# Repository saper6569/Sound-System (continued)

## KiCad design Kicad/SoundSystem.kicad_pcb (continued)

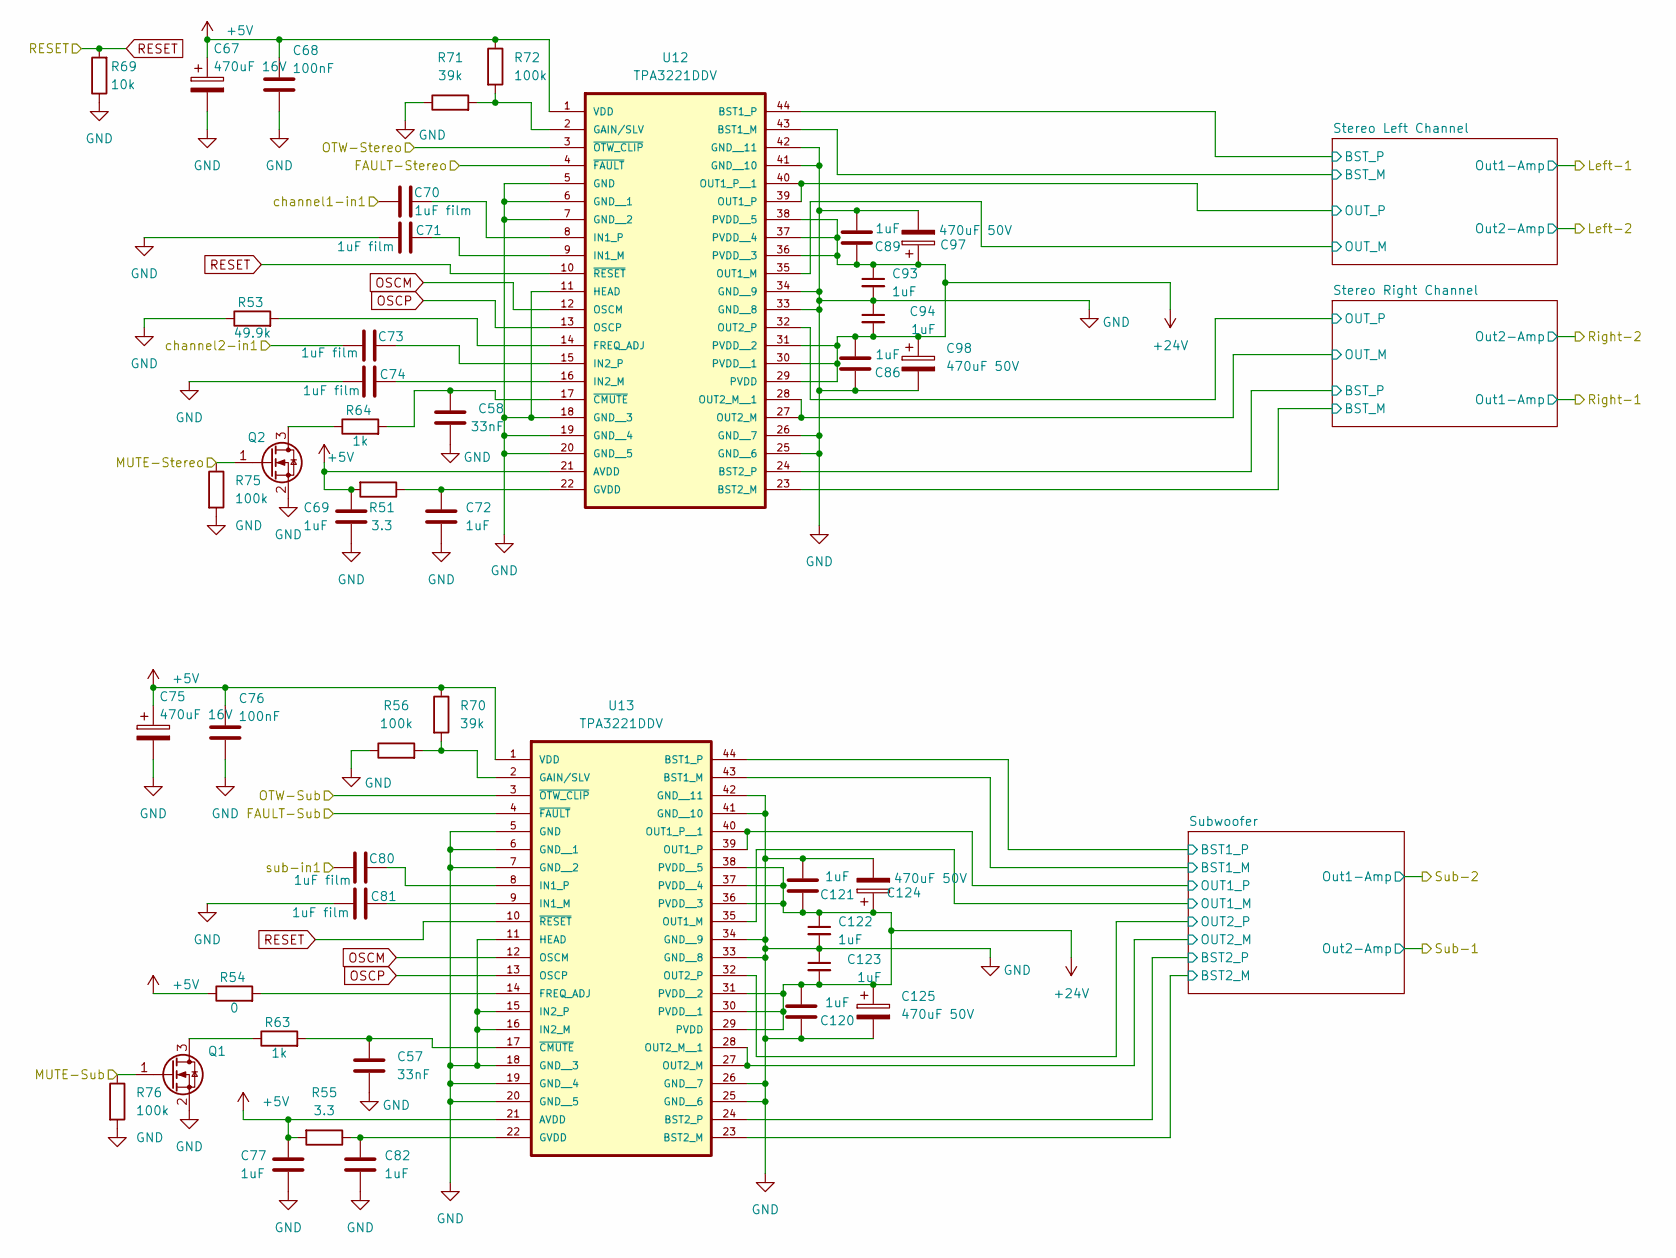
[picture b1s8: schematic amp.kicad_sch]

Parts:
C57, C58: 33nF; C_0805_2012Metric_Pad1.18x1.45mm_HandSolder; MPN CC0805KRX7R9BB333; LCSC C107150
C67, C75: 470uF 16V; CP_Elec_10x10; MPN RYRVT16V470UF10*10; LCSC C48970774
C68, C76: 100nF; C_0805_2012Metric_Pad1.18x1.45mm_HandSolder; MPN CC0805KRX7R9BB104; LCSC C49678
C69, C72, C77, C82: 1uF; C_0805_2012Metric_Pad1.18x1.45mm_HandSolder; MPN CC0805KKX7R9BB105; LCSC C91185
C70, C71, C73, C74, C80, C81: 1uF film; C_Rect_L7.2mm_W5.5mm_P5.00mm_FKS2_FKP2_MKS2_MKP2; MPN B32529C0105J289; LCSC C125386
C86, C89, C93, C94, C120, C121, C122, C123: 1uF; C_1206_3216Metric_Pad1.33x1.80mm_HandSolder; MPN CC1206KKX7R9BB105; LCSC C107185
C97, C98, C124, C125: 470uF 50V; CP_Radial_D12.5mm_P5.00mm; MPN NXH 50V470 12.5*20; LCSC C165672
Q1, Q2: 2N7002; TO-236AB_SOT23_NEX; MPN 2N7002; LCSC C8545
R51, R55: 3.3; R_0603_1608Metric_Pad0.98x0.95mm_HandSolder; MPN 0603WAF330KT5E; LCSC C22979
R53: 49.9k; R_0805_2012Metric_Pad1.20x1.40mm_HandSolder; MPN 0805W8F4992T5E; LCSC C17719
R54: 0; R_0805_2012Metric_Pad1.20x1.40mm_HandSolder; MPN 0805W8F0000T5E; LCSC C17477
R56, R72: 100k; R_0603_1608Metric_Pad0.98x0.95mm_HandSolder; MPN 0603WAF1003T5E; LCSC C25803
R63, R64: 1k; R_0805_2012Metric_Pad1.20x1.40mm_HandSolder; MPN 0805W8F1001T5E; LCSC C17513
R69: 10k; R_0805_2012Metric_Pad1.20x1.40mm_HandSolder; MPN 0805W8F1002T5E; LCSC C17414
R70, R71: 39k; R_0805_2012Metric_Pad1.20x1.40mm_HandSolder; MPN 0805W8F3902T5E; LCSC C25826
R75, R76: 100k; R_0805_2012Metric_Pad1.20x1.40mm_HandSolder; MPN 0805W8F1003T5E; LCSC C17407
U12, U13: TPA3221DDV; MPN TPA3221DDVR; LCSC C475500

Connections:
/Amplifier/FAULT-Stereo: U12.4 (~FAULT); also elsewhere on the board
/Amplifier/FAULT-Sub: U13.4 (~FAULT); also elsewhere on the board
/Amplifier/MUTE-Stereo: Q2.1 (G), R75.1; also elsewhere on the board
/Amplifier/MUTE-Sub: Q1.1 (G), R76.1; also elsewhere on the board
/Amplifier/OTW-Stereo: U12.3 (~OTW_CLIP); also elsewhere on the board
/Amplifier/OTW-Sub: U13.3 (~OTW_CLIP); also elsewhere on the board
/Amplifier/Stereo Left Channel/BST_M: U12.43 (BST1_M); also elsewhere on the board
/Amplifier/Stereo Left Channel/BST_P: U12.44 (BST1_P); also elsewhere on the board
/Amplifier/Stereo Left Channel/OUT_M: U12.35 (OUT1_M); also elsewhere on the board
/Amplifier/Stereo Left Channel/OUT_P: U12.39 (OUT1_P), U12.40 (OUT1_P__1); also elsewhere on the board
/Amplifier/Stereo Right Channel/BST_M: U12.23 (BST2_M); also elsewhere on the board
/Amplifier/Stereo Right Channel/BST_P: U12.24 (BST2_P); also elsewhere on the board
/Amplifier/Stereo Right Channel/OUT_M: U12.27 (OUT2_M), U12.28 (OUT2_M__1); also elsewhere on the board
/Amplifier/Stereo Right Channel/OUT_P: U12.32 (OUT2_P); also elsewhere on the board
/Amplifier/Subwoofer/BST1_M: U13.43 (BST1_M); also elsewhere on the board
/Amplifier/Subwoofer/BST1_P: U13.44 (BST1_P); also elsewhere on the board
/Amplifier/Subwoofer/BST2_M: U13.23 (BST2_M); also elsewhere on the board
/Amplifier/Subwoofer/BST2_P: U13.24 (BST2_P); also elsewhere on the board
/Amplifier/Subwoofer/OUT1_M: U13.27 (OUT2_M), U13.28 (OUT2_M__1), U13.35 (OUT1_M); also elsewhere on the board
/Amplifier/Subwoofer/OUT1_P: U13.32 (OUT2_P), U13.39 (OUT1_P), U13.40 (OUT1_P__1); also elsewhere on the board
/Amplifier/channel1-in1: C70.1; also elsewhere on the board
/Amplifier/channel2-in1: C73.1; also elsewhere on the board
/Amplifier/sub-in1: C80.1; also elsewhere on the board
GND: C57.2, C58.2, C67.2, C68.2, C69.2, C71.1, C72.2, C74.1, C75.2, C76.2, C77.2, C81.1, C82.2, C86.1, C89.2, C93.2, C94.1, C97.2, C98.2, C120.1, C121.2, C122.2, C123.1, C124.2, C125.2, Q1.2 (S), Q2.2 (S), R53.1, R56.1, R69.1, R71.1, R75.2, R76.2, U12.5 (GND), U12.6 (GND__1), U12.7 (GND__2), U12.11 (HEAD), U12.18 (GND__3), U12.19 (GND__4), U12.20 (GND__5), U12.25 (GND__6), U12.26 (GND__7), U12.33 (GND__8), U12.34 (GND__9), U12.41 (GND__10), U12.42 (GND__11), U13.5 (GND), U13.6 (GND__1), U13.7 (GND__2), U13.11 (HEAD), U13.15 (IN2_P), U13.16 (IN2_M), U13.18 (GND__3), U13.19 (GND__4), U13.20 (GND__5), U13.25 (GND__6), U13.26 (GND__7), U13.33 (GND__8), U13.34 (GND__9), U13.41 (GND__10), U13.42 (GND__11); also elsewhere on the board
unnamed: Q1.3 (D), R63.1
unnamed: Q2.3 (D), R64.1
unnamed: R53.2, U12.14 (FREQ_ADJ)
unnamed: R71.2, R72.2, U12.2 (GAIN/SLV)
unnamed: C72.1, R51.1, U12.22 (GVDD)
unnamed: C71.2, U12.9 (IN1_M)
unnamed: C70.2, U12.8 (IN1_P)
unnamed: C74.2, U12.16 (IN2_M)
unnamed: C73.2, U12.15 (IN2_P)
unnamed: C58.1, R64.2, U12.17 (~CMUTE)
unnamed: R54.2, U13.14 (FREQ_ADJ)
unnamed: R56.2, R70.2, U13.2 (GAIN/SLV)
unnamed: C82.1, R55.1, U13.22 (GVDD)
unnamed: C81.2, U13.9 (IN1_M)
unnamed: C80.2, U13.8 (IN1_P)
unnamed: C57.1, R63.2, U13.17 (~CMUTE)
OSCM: U12.12 (OSCM), U13.12 (OSCM)
OSCP: U12.13 (OSCP), U13.13 (OSCP)
RESET: R69.2, U12.10 (~RESET), U13.10 (~RESET); also elsewhere on the board

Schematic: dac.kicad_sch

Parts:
C44, C52, C53, C54: 100nF; C_0805_2012Metric_Pad1.18x1.45mm_HandSolder; MPN CC0805KRX7R9BB104; LCSC C49678
C46, C51, C55, C56: 10uF; C_0603_1608Metric_Pad1.08x0.95mm_HandSolder; MPN CL10A106KP8NNNC; LCSC C19702
C47, C48: 2.2nF; C_0805_2012Metric_Pad1.18x1.45mm_HandSolder; MPN 0805N222J500CT; LCSC C303929
C49, C50: 2.2uF; C_0603_1608Metric_Pad1.08x0.95mm_HandSolder; MPN CL10A225KO8NNNC; LCSC C23630
R1: 10k; R_0805_2012Metric_Pad1.20x1.40mm_HandSolder; MPN 0805W8F1002T5E; LCSC C17414
R8, R46: 470; R_0805_2012Metric_Pad1.20x1.40mm_HandSolder; MPN 0805W8F4700T5E; LCSC C17710
U14: PCM5102A; TSSOP-20_4.4x6.5mm_P0.65mm; MPN PCM5102APW; LCSC C1520792

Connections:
+3.3V: C44.2, C46.1, C51.1, C52.1, C54.1, C56.1, U14.1 (CPVDD), U14.8 (AVDD), U14.20 (DVDD); also elsewhere on the board
/Microcontroller/Left Channel: C48.1, R8.2; also elsewhere on the board
/Microcontroller/Right Channel: C47.2, R46.2; also elsewhere on the board
BCK: U14.13 (BCK); also elsewhere on the board
DIN: U14.14 (DIN); also elsewhere on the board
GND: C44.1, C46.2, C47.1, C48.2, C50.1, C51.2, C52.2, C53.1, C54.2, C55.2, C56.2, R1.2, U14.3 (CPGND), U14.9 (AGND), U14.10 (DEMP), U14.11 (FLT), U14.12 (SCK), U14.16 (FMT), U14.19 (DGND); also elsewhere on the board
LRCK: U14.15 (LRCK); also elsewhere on the board
unnamed: C49.1, U14.4 (CAPM)
unnamed: C49.2, U14.2 (CAPP)
unnamed: C53.2, C55.1, U14.18 (LDOO)
unnamed: R8.1, U14.6 (OUTL)
unnamed: R46.1, U14.7 (OUTR)
unnamed: C50.2, U14.5 (VNEG)
XSMT: R1.1, U14.17 (XSMT); also elsewhere on the board

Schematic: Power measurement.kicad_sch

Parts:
C59: 1uF; C_0805_2012Metric_Pad1.18x1.45mm_HandSolder; MPN CC0805KKX7R9BB105; LCSC C91185
R67, R68: 10k; R_0805_2012Metric_Pad1.20x1.40mm_HandSolder; MPN 0805W8F1002T5E; LCSC C17414
U1: INA226; TSSOP-10_3x3mm_P0.5mm; MPN INA226AIDGSR; LCSC C49851

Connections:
+3.3V: C59.1, R67.1, R68.1, U1.6 (VS); also elsewhere on the board
/Microcontroller/In+: U1.10 (Vin+); also elsewhere on the board
/Microcontroller/In-: U1.8 (Vbus), U1.9 (Vin-); also elsewhere on the board
GND: C59.2, U1.1 (A1), U1.2 (A0), U1.7 (GND); also elsewhere on the board
SCL: R68.2, U1.5 (SCL); also elsewhere on the board
SDA: R67.2, U1.4 (SDA); also elsewhere on the board

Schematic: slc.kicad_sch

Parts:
C87, C88: 33nF; C_0805_2012Metric_Pad1.18x1.45mm_HandSolder; MPN CC0805KRX7R9BB333; LCSC C107150
C91, C92: 1uF 100V film; C_Rect_L10.3mm_W7.2mm_P7.50mm_MKS4; MPN MPE105J100V82CL0042; LCSC C2831916
C95, C96: 1nF film; C_Rect_L7.2mm_W3.5mm_P5.00mm_FKS2_FKP2_MKS2_MKP2; MPN C242A102J20C000; LCSC C280714
C99, C100: 10nF; C_0603_1608Metric_Pad1.08x0.95mm_HandSolder; MPN CC0603KRX7R9BB103; LCSC C100042
L6, L7: 10uH; L_TaiTech_TMPC1265_13.5x12.5mm; MPN TMPC1265HP-100MG-D; LCSC C305223
R57, R58: 3.3; R_0603_1608Metric_Pad0.98x0.95mm_HandSolder; MPN 0603WAF330KT5E; LCSC C22979

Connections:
/Amplifier/Left-1: C91.1, C95.1, C99.2, L6.2; also elsewhere on the board
/Amplifier/Left-2: C92.2, C96.2, C100.1, L7.2; also elsewhere on the board
/Amplifier/Stereo Left Channel/BST_M: C88.1; also elsewhere on the board
/Amplifier/Stereo Left Channel/BST_P: C87.1; also elsewhere on the board
/Amplifier/Stereo Left Channel/OUT_M: C88.2, L7.1; also elsewhere on the board
/Amplifier/Stereo Left Channel/OUT_P: C87.2, L6.1; also elsewhere on the board
GND: C91.2, C92.1, C95.2, C96.1, R57.1, R58.2; also elsewhere on the board
unnamed: C99.1, R57.2
unnamed: C100.2, R58.1

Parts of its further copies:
C90, C101: 33nF; C_0805_2012Metric_Pad1.18x1.45mm_HandSolder; MPN CC0805KRX7R9BB333; LCSC C107150
C102, C103: 1uF 100V film; C_Rect_L10.3mm_W7.2mm_P7.50mm_MKS4; MPN MPE105J100V82CL0042; LCSC C2831916
C104, C105: 1nF film; C_Rect_L7.2mm_W3.5mm_P5.00mm_FKS2_FKP2_MKS2_MKP2; MPN C242A102J20C000; LCSC C280714
C106, C107: 10nF; C_0603_1608Metric_Pad1.08x0.95mm_HandSolder; MPN CC0603KRX7R9BB103; LCSC C100042
L8, L9: 10uH; L_TaiTech_TMPC1265_13.5x12.5mm; MPN TMPC1265HP-100MG-D; LCSC C305223
R59, R60: 3.3; R_0603_1608Metric_Pad0.98x0.95mm_HandSolder; MPN 0603WAF330KT5E; LCSC C22979

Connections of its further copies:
/Amplifier/Right-1: C102.1, C104.1, C106.2, L8.2; also elsewhere on the board
/Amplifier/Right-2: C103.2, C105.2, C107.1, L9.2; also elsewhere on the board
/Amplifier/Stereo Right Channel/BST_M: C101.1; also elsewhere on the board
/Amplifier/Stereo Right Channel/BST_P: C90.1; also elsewhere on the board
/Amplifier/Stereo Right Channel/OUT_M: C101.2, L9.1; also elsewhere on the board
/Amplifier/Stereo Right Channel/OUT_P: C90.2, L8.1; also elsewhere on the board
GND: C102.2, C103.1, C104.2, C105.1, R59.1, R60.2; also elsewhere on the board
unnamed: C106.1, R59.2
unnamed: C107.2, R60.1

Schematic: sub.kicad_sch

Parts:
C108, C109, C116, C117: 33nF; C_0805_2012Metric_Pad1.18x1.45mm_HandSolder; MPN CC0805KRX7R9BB333; LCSC C107150
C110, C111, C118, C119: 470nF 100V film; C_Rect_L10.3mm_W7.2mm_P7.50mm_MKS4; MPN B32560J1474K000; LCSC C125398
C112, C113: 1nF film; C_Rect_L7.2mm_W3.5mm_P5.00mm_FKS2_FKP2_MKS2_MKP2; MPN C242A102J20C000; LCSC C280714
C114, C115: 10nF; C_0603_1608Metric_Pad1.08x0.95mm_HandSolder; MPN CC0603KRX7R9BB103; LCSC C100042
L10, L11: 10uH; L_SXN_SMMS1770; MPN SMMS1770-100M; LCSC C2976967
R61, R62: 3.3; R_0603_1608Metric_Pad0.98x0.95mm_HandSolder; MPN 0603WAF330KT5E; LCSC C22979

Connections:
/Amplifier/Sub-1: C111.2, C113.2, C115.1, C119.2, L11.2; also elsewhere on the board
/Amplifier/Sub-2: C110.1, C112.1, C114.2, C118.1, L10.2; also elsewhere on the board
/Amplifier/Subwoofer/BST1_M: C109.1; also elsewhere on the board
/Amplifier/Subwoofer/BST1_P: C108.1; also elsewhere on the board
/Amplifier/Subwoofer/BST2_M: C116.1; also elsewhere on the board
/Amplifier/Subwoofer/BST2_P: C117.1; also elsewhere on the board
/Amplifier/Subwoofer/OUT1_M: C109.2, C116.2, L11.1; also elsewhere on the board
/Amplifier/Subwoofer/OUT1_P: C108.2, C117.2, L10.1; also elsewhere on the board
GND: C110.2, C111.1, C112.2, C113.1, C118.2, C119.1, R61.1, R62.2; also elsewhere on the board
unnamed: C114.1, R61.2
unnamed: C115.2, R62.1

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
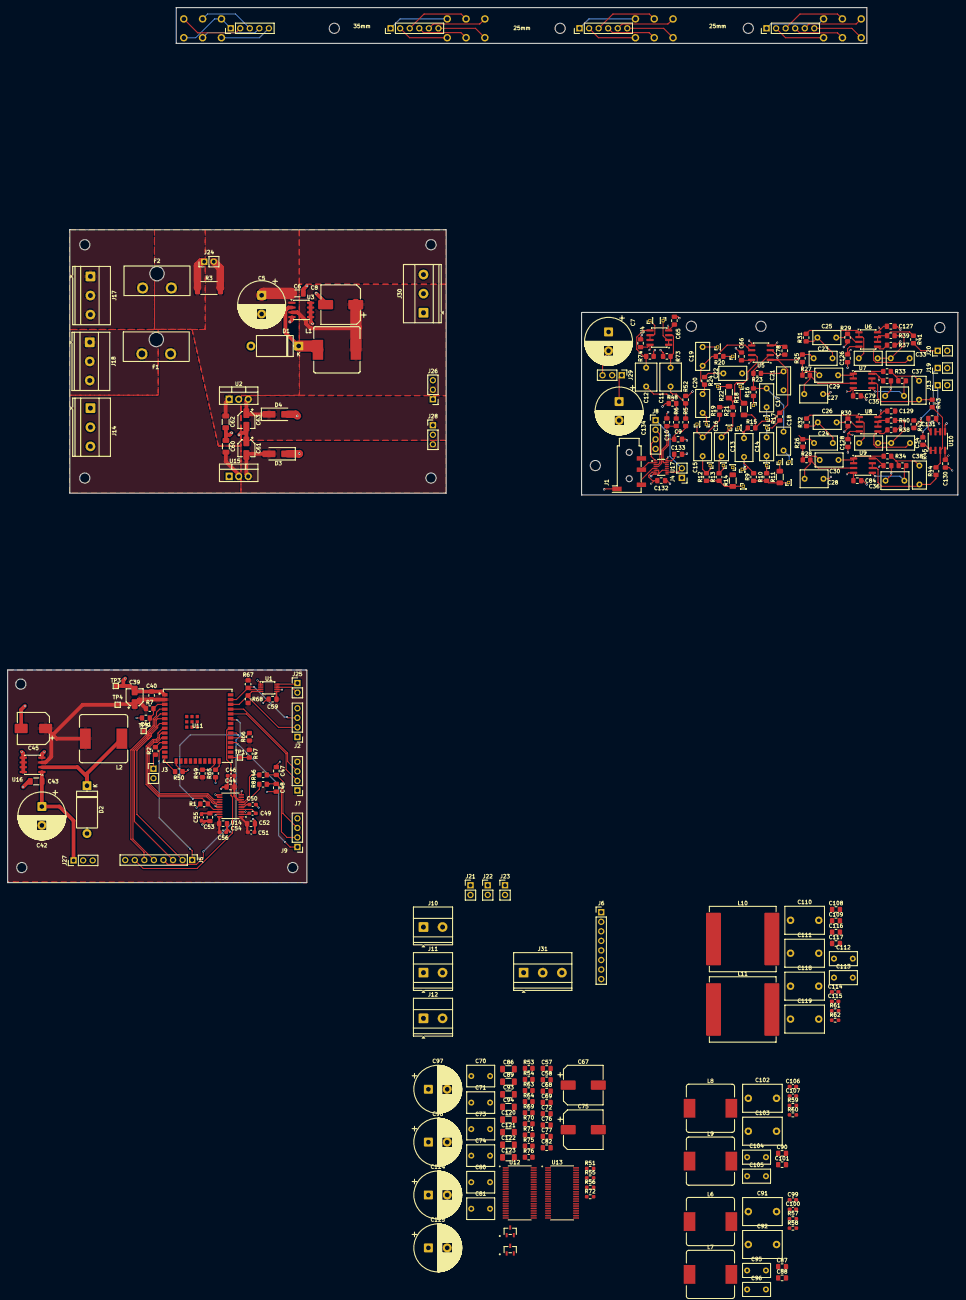
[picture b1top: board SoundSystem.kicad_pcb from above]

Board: 4 copper layers, 275 parts (0 on the bottom side), 169 nets.
